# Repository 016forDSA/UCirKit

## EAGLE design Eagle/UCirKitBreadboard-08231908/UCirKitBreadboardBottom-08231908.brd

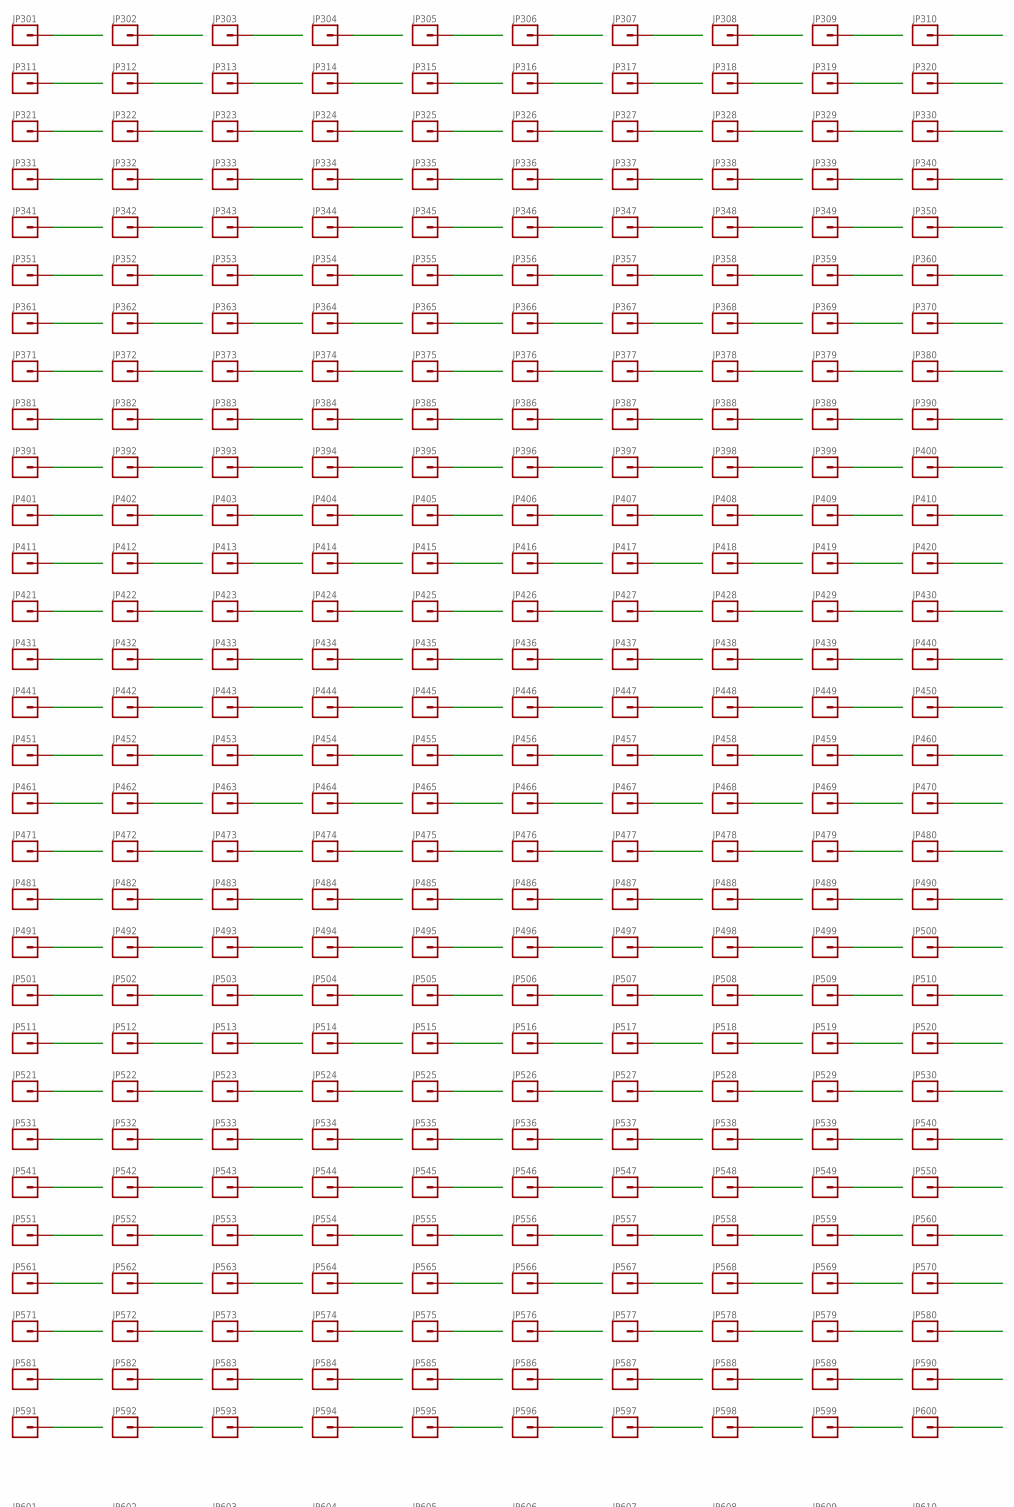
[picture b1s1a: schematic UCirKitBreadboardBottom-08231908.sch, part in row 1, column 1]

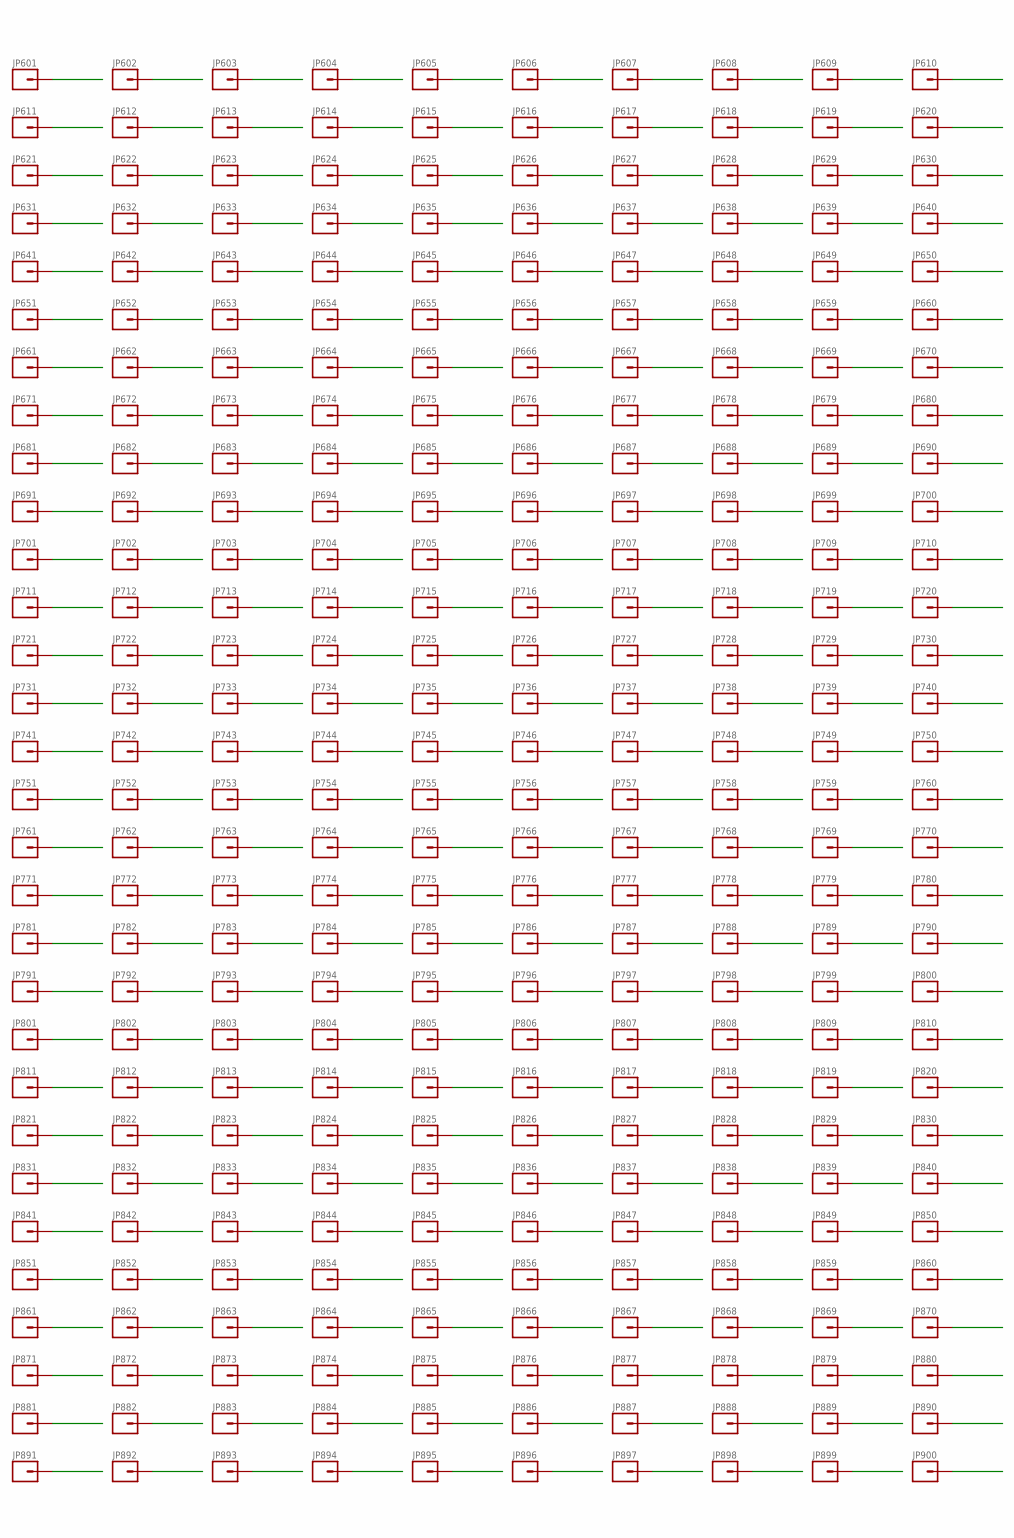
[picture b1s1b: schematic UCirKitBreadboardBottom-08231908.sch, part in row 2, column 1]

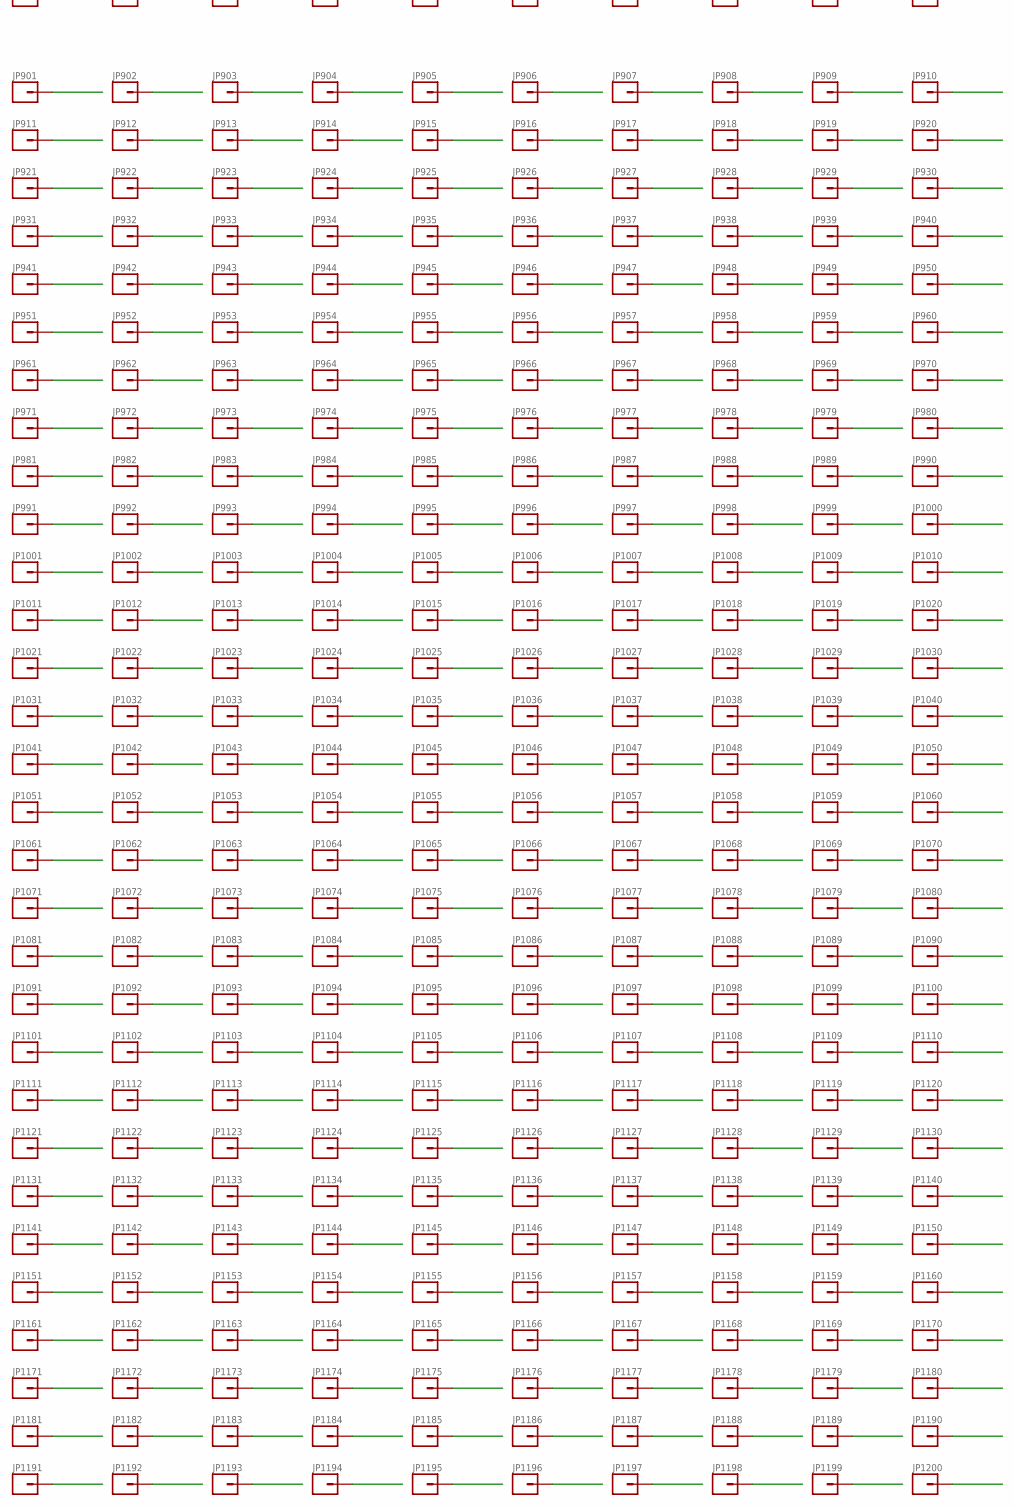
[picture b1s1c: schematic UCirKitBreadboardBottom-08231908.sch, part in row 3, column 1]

Parts:
JP301, JP302, JP303, JP304, JP305, JP306, JP307, JP308, JP309, JP310, JP311, JP312, JP313, JP314, JP315, JP316, JP317, JP318, JP319, JP320, JP321, JP322, JP323, JP324, JP325, JP326, JP327, JP328, JP329, JP330, JP331, JP332, JP333, JP334, JP335, JP336, JP337, JP338, JP339, JP340, JP341, JP342, JP343, JP344, JP345, JP346, JP347, JP348, JP349, JP350, JP351, JP352, JP353, JP354, JP355, JP356, JP357, JP358, JP359, JP360, JP361, JP362, JP363, JP364, JP365, JP366, JP367, JP368, JP369, JP370, JP371, JP372, JP373, JP374, JP375, JP376, JP377, JP378, JP379, JP380, JP381, JP382, JP383, JP384, JP385, JP386, JP387, JP388, JP389, JP390, JP391, JP392, JP393, JP394, JP395, JP396, JP397, JP398, JP399, JP400, JP401, JP402, JP403, JP404, JP405, JP406, JP407, JP408, JP409, JP410, JP411, JP412, JP413, JP414, JP415, JP416, JP417, JP418, JP419, JP420, JP421, JP422, JP423, JP424, JP425, JP426, JP427, JP428, JP429, JP430, JP431, JP432, JP433, JP434, JP435, JP436, JP437, JP438, JP439, JP440, JP441, JP442, JP443, JP444, JP445, JP446, JP447, JP448, JP449, JP450, JP451, JP452, JP453, JP454, JP455, JP456, JP457, JP458, JP459, JP460, JP461, JP462, JP463, JP464, JP465, JP466, JP467, JP468, JP469, JP470, JP471, JP472, JP473, JP474, JP475, JP476, JP477, JP478, JP479, JP480, JP481, JP482, JP483, JP484, JP485, JP486, JP487, JP488, JP489, JP490, JP491, JP492, JP493, JP494, JP495, JP496, JP497, JP498, JP499, JP500, JP501, JP502, JP503, JP504, JP505, JP506, JP507, JP508, JP509, JP510, JP511, JP512, JP513, JP514, JP515, JP516, JP517, JP518, JP519, JP520, JP521, JP522, JP523, JP524, JP525, JP526, JP527, JP528, JP529, JP530, JP531, JP532, JP533, JP534, JP535, JP536, JP537, JP538, JP539, JP540, JP541, JP542, JP543, JP544, JP545, JP546, JP547, JP548, JP549, JP550, JP551, JP552, JP553, JP554, JP555, JP556, JP557, JP558, JP559, JP560, JP561, JP562, JP563, JP564, JP565, JP566, JP567, JP568, JP569, JP570, JP571, JP572, JP573, JP574, JP575, JP576, JP577, JP578, JP579, JP580, JP581, JP582, JP583, JP584, JP585, JP586, JP587, JP588, JP589, JP590, JP591, JP592, JP593, JP594, JP595, JP596, JP597, JP598, JP599, JP600, JP601, JP602, JP603, JP604, JP605, JP606, JP607, JP608, JP609, JP610, JP611, JP612, JP613, JP614, JP615, JP616, JP617, JP618, JP619, JP620, JP621, JP622, JP623, JP624, JP625, JP626, JP627, JP628, JP629, JP630, JP631, JP632, JP633, JP634, JP635, JP636, JP637, JP638, JP639, JP640, JP641, JP642, JP643, JP644, JP645, JP646, JP647, JP648, JP649, JP650, JP651, JP652, JP653, JP654, JP655, JP656, JP657, JP658, JP659, JP660, JP661, JP662, JP663, JP664, JP665, JP666, JP667, JP668, JP669, JP670, JP671, JP672, JP673, JP674, JP675, JP676, JP677, JP678, JP679, JP680, JP681, JP682, JP683, JP684, JP685, JP686, JP687, JP688, JP689, JP690, JP691, JP692, JP693, JP694, JP695, JP696, JP697, JP698, JP699, JP700, JP701, JP702, JP703, JP704, JP705, JP706, JP707, JP708, JP709, JP710, JP711, JP712, JP713, JP714, JP715, JP716, JP717, JP718, JP719, JP720, JP721, JP722, JP723, JP724, JP725, JP726, JP727, JP728, JP729, JP730, JP731, JP732, JP733, JP734, JP735, JP736, JP737, JP738, JP739, JP740, JP741, JP742, JP743, JP744, JP745, JP746, JP747, JP748, JP749, JP750, JP751, JP752, JP753, JP754, JP755, JP756, JP757, JP758, JP759, JP760, JP761, JP762, JP763, JP764, JP765, JP766, JP767, JP768, JP769, JP770, JP771, JP772, JP773, JP774, JP775, JP776, JP777, JP778, JP779, JP780, JP781, JP782, JP783, JP784, JP785, JP786, JP787, JP788, JP789, JP790, JP791, JP792, JP793, JP794, JP795, JP796, JP797, JP798, JP799, JP800, JP801, JP802, JP803, JP804, JP805, JP806, JP807, JP808, JP809, JP810, JP811, JP812, JP813, JP814, JP815, JP816, JP817, JP818, JP819, JP820, JP821, JP822, JP823, JP824, JP825, JP826, JP827, JP828, JP829, JP830, JP831, JP832, JP833, JP834, JP835, JP836, JP837, JP838, JP839, JP840, JP841, JP842, JP843, JP844, JP845, JP846, JP847, JP848, JP849, JP850, JP851, JP852, JP853, JP854, JP855, JP856, JP857, JP858, JP859, JP860, JP861, JP862, JP863, JP864, JP865, JP866, JP867, JP868, JP869, JP870, JP871, JP872, JP873, JP874, JP875, JP876, JP877, JP878, JP879, JP880, JP881, JP882, JP883, JP884, JP885, JP886, JP887, JP888, JP889, JP890, JP891, JP892, JP893, JP894, JP895, JP896, JP897, JP898, JP899, JP900, JP901, JP902, JP903, JP904, JP905, JP906, JP907, JP908, JP909, JP910, JP911, JP912, JP913, JP914, JP915, JP916, JP917, JP918, JP919, JP920, JP921, JP922, JP923, JP924, JP925, JP926, JP927, JP928, JP929, JP930, JP931, JP932, JP933, JP934, JP935, JP936, JP937, JP938, JP939, JP940, JP941, JP942, JP943, JP944, JP945, JP946, JP947, JP948, JP949, JP950, JP951, JP952, JP953, JP954, JP955, JP956, JP957, JP958, JP959, JP960, JP961, JP962, JP963, JP964, JP965, JP966, JP967, JP968, JP969, JP970, JP971, JP972, JP973, JP974, JP975, JP976, JP977, JP978, JP979, JP980, JP981, JP982, JP983, JP984, JP985, JP986, JP987, JP988, JP989, JP990, JP991, JP992, JP993, JP994, JP995, JP996, JP997, JP998, JP999, JP1000, JP1001, JP1002, JP1003, JP1004, JP1005, JP1006, JP1007, JP1008, JP1009, JP1010, JP1011, JP1012, JP1013, JP1014, JP1015, JP1016, JP1017, JP1018, JP1019, JP1020, JP1021, JP1022, JP1023, JP1024, JP1025, JP1026, JP1027, JP1028, JP1029, JP1030, JP1031, JP1032, JP1033, JP1034, JP1035, JP1036, JP1037, JP1038, JP1039, JP1040, JP1041, JP1042, JP1043, JP1044, JP1045, JP1046, JP1047, JP1048, JP1049, JP1050, JP1051, JP1052, JP1053, JP1054, JP1055, JP1056, JP1057, JP1058, JP1059, JP1060, JP1061, JP1062, JP1063, JP1064, JP1065, JP1066, JP1067, JP1068, JP1069, JP1070, JP1071, JP1072, JP1073, JP1074, JP1075, JP1076, JP1077, JP1078, JP1079, JP1080, JP1081, JP1082, JP1083, JP1084, JP1085, JP1086, JP1087, JP1088, JP1089, JP1090, JP1091, JP1092, JP1093, JP1094, JP1095, JP1096, JP1097, JP1098, JP1099, JP1100, JP1101, JP1102, JP1103, JP1104, JP1105, JP1106, JP1107, JP1108, JP1109, JP1110, JP1111, JP1112, JP1113, JP1114, JP1115, JP1116, JP1117, JP1118, JP1119, JP1120, JP1121, JP1122, JP1123, JP1124, JP1125, JP1126, JP1127, JP1128, JP1129, JP1130, JP1131, JP1132, JP1133, JP1134, JP1135, JP1136, JP1137, JP1138, JP1139, JP1140, JP1141, JP1142, JP1143, JP1144, JP1145, JP1146, JP1147, JP1148, JP1149, JP1150, JP1151, JP1152, JP1153, JP1154, JP1155, JP1156, JP1157, JP1158, JP1159, JP1160, JP1161, JP1162, JP1163, JP1164, JP1165, JP1166, JP1167, JP1168, JP1169, JP1170, JP1171, JP1172, JP1173, JP1174, JP1175, JP1176, JP1177, JP1178, JP1179, JP1180, JP1181, JP1182, JP1183, JP1184, JP1185, JP1186, JP1187, JP1188, JP1189, JP1190, JP1191, JP1192, JP1193, JP1194, JP1195, JP1196, JP1197, JP1198, JP1199, JP1200: M01PTH_SMD_3.25X0.85MM_NO_SILK; 1X01_SMD_3.25X0.85MM_NO_SILK

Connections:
0_1440338354: JP301.P$1, JP661.P$1, JP961.P$1
0_1440338422: JP305.P$1, JP851.P$1, JP1151.P$1
0_1440338442: JP306.P$1, JP859.P$1, JP1159.P$1
1_1440338354: JP311.P$1, JP663.P$1, JP963.P$1
1_1440338422: JP315.P$1, JP852.P$1, JP1152.P$1
1_1440338442: JP316.P$1, JP860.P$1, JP1160.P$1
2_1440338354: JP321.P$1, JP665.P$1, JP965.P$1
2_1440338422: JP595.P$1, JP881.P$1, JP1181.P$1
2_1440338442: JP596.P$1, JP889.P$1, JP1189.P$1
3_1440338354: JP331.P$1, JP667.P$1, JP967.P$1
3_1440338422: JP585.P$1, JP882.P$1, JP1182.P$1
3_1440338442: JP586.P$1, JP890.P$1, JP1190.P$1
4_1440338354: JP341.P$1, JP669.P$1, JP969.P$1
4_1440338422: JP325.P$1, JP850.P$1, JP1150.P$1
4_1440338442: JP326.P$1, JP858.P$1, JP1158.P$1
5_1440338354: JP351.P$1, JP671.P$1, JP971.P$1
5_1440338422: JP335.P$1, JP853.P$1, JP1153.P$1
5_1440338442: JP336.P$1, JP861.P$1, JP1161.P$1
6_1440338354: JP361.P$1, JP673.P$1, JP973.P$1
6_1440338422: JP575.P$1, JP880.P$1, JP1180.P$1
6_1440338442: JP576.P$1, JP888.P$1, JP1188.P$1
7_1440338354: JP371.P$1, JP675.P$1, JP975.P$1
7_1440338422: JP565.P$1, JP883.P$1, JP1183.P$1
7_1440338442: JP566.P$1, JP891.P$1, JP1191.P$1
8_1440338354: JP381.P$1, JP677.P$1, JP977.P$1
8_1440338422: JP345.P$1, JP849.P$1, JP1149.P$1
8_1440338442: JP346.P$1, JP857.P$1, JP1157.P$1
9_1440338354: JP391.P$1, JP679.P$1, JP979.P$1
9_1440338422: JP355.P$1, JP854.P$1, JP1154.P$1
9_1440338442: JP356.P$1, JP862.P$1, JP1162.P$1
10_1440338354: JP401.P$1, JP681.P$1, JP981.P$1
10_1440338422: JP555.P$1, JP879.P$1, JP1179.P$1
10_1440338442: JP556.P$1, JP887.P$1, JP1187.P$1
11_1440338354: JP411.P$1, JP683.P$1, JP983.P$1
11_1440338422: JP545.P$1, JP884.P$1, JP1184.P$1
11_1440338442: JP546.P$1, JP892.P$1, JP1192.P$1
12_1440338354: JP421.P$1, JP685.P$1, JP985.P$1
12_1440338422: JP365.P$1, JP848.P$1, JP1148.P$1
12_1440338442: JP366.P$1, JP856.P$1, JP1156.P$1
13_1440338354: JP431.P$1, JP687.P$1, JP987.P$1
13_1440338422: JP375.P$1, JP855.P$1, JP1155.P$1
13_1440338442: JP376.P$1, JP863.P$1, JP1163.P$1
14_1440338354: JP441.P$1, JP689.P$1, JP989.P$1
14_1440338422: JP535.P$1, JP878.P$1, JP1178.P$1
14_1440338442: JP386.P$1, JP864.P$1, JP1164.P$1
15_1440338354: JP451.P$1, JP691.P$1, JP991.P$1
15_1440338422: JP525.P$1, JP885.P$1, JP1185.P$1
15_1440338442: JP396.P$1, JP865.P$1, JP1165.P$1
16_1440338354: JP461.P$1, JP693.P$1, JP993.P$1
16_1440338422: JP385.P$1, JP847.P$1, JP1147.P$1
16_1440338442: JP406.P$1, JP866.P$1, JP1166.P$1
17_1440338354: JP471.P$1, JP695.P$1, JP995.P$1
17_1440338422: JP515.P$1, JP877.P$1, JP1177.P$1
17_1440338442: JP416.P$1, JP867.P$1, JP1167.P$1
18_1440338354: JP481.P$1, JP697.P$1, JP997.P$1
18_1440338422: JP395.P$1, JP846.P$1, JP1146.P$1
18_1440338442: JP426.P$1, JP868.P$1, JP1168.P$1
19_1440338354: JP491.P$1, JP699.P$1, JP999.P$1
19_1440338422: JP505.P$1, JP876.P$1, JP1176.P$1
19_1440338442: JP436.P$1, JP869.P$1, JP1169.P$1
20_1440338354: JP501.P$1, JP701.P$1, JP1001.P$1
20_1440338422: JP405.P$1, JP845.P$1, JP1145.P$1
20_1440338442: JP446.P$1, JP870.P$1, JP1170.P$1
21_1440338354: JP511.P$1, JP703.P$1, JP1003.P$1
21_1440338422: JP495.P$1, JP875.P$1, JP1175.P$1
21_1440338442: JP536.P$1, JP886.P$1, JP1186.P$1
22_1440338354: JP521.P$1, JP705.P$1, JP1005.P$1
22_1440338422: JP415.P$1, JP844.P$1, JP1144.P$1
22_1440338442: JP526.P$1, JP893.P$1, JP1193.P$1
23_1440338354: JP531.P$1, JP707.P$1, JP1007.P$1
23_1440338422: JP485.P$1, JP874.P$1, JP1174.P$1
23_1440338442: JP516.P$1, JP894.P$1, JP1194.P$1
24_1440338354: JP541.P$1, JP709.P$1, JP1009.P$1
24_1440338422: JP425.P$1, JP843.P$1, JP1143.P$1
24_1440338442: JP506.P$1, JP895.P$1, JP1195.P$1
25_1440338354: JP551.P$1, JP711.P$1, JP1011.P$1
25_1440338422: JP475.P$1, JP873.P$1, JP1173.P$1
25_1440338442: JP496.P$1, JP896.P$1, JP1196.P$1
26_1440338354: JP561.P$1, JP713.P$1, JP1013.P$1
26_1440338422: JP435.P$1, JP842.P$1, JP1142.P$1
26_1440338442: JP486.P$1, JP897.P$1, JP1197.P$1
27_1440338354: JP571.P$1, JP715.P$1, JP1015.P$1
27_1440338422: JP465.P$1, JP872.P$1, JP1172.P$1
27_1440338442: JP476.P$1, JP898.P$1, JP1198.P$1
28_1440338354: JP581.P$1, JP717.P$1, JP1017.P$1
28_1440338422: JP445.P$1, JP841.P$1, JP1141.P$1
28_1440338442: JP466.P$1, JP899.P$1, JP1199.P$1
29_1440338354: JP591.P$1, JP719.P$1, JP1019.P$1
29_1440338422: JP455.P$1, JP871.P$1, JP1171.P$1
29_1440338442: JP456.P$1, JP900.P$1, JP1200.P$1
30_1440338354: JP592.P$1, JP720.P$1, JP1020.P$1
31_1440338354: JP310.P$1, JP721.P$1, JP1021.P$1
32_1440338354: JP320.P$1, JP723.P$1, JP1023.P$1
33_1440338354: JP330.P$1, JP725.P$1, JP1025.P$1
34_1440338354: JP340.P$1, JP727.P$1, JP1027.P$1
35_1440338354: JP350.P$1, JP729.P$1, JP1029.P$1
36_1440338354: JP360.P$1, JP731.P$1, JP1031.P$1
37_1440338354: JP370.P$1, JP733.P$1, JP1033.P$1
38_1440338354: JP380.P$1, JP735.P$1, JP1035.P$1
39_1440338354: JP390.P$1, JP737.P$1, JP1037.P$1
40_1440338354: JP400.P$1, JP739.P$1, JP1039.P$1
41_1440338354: JP410.P$1, JP741.P$1, JP1041.P$1
42_1440338354: JP420.P$1, JP743.P$1, JP1043.P$1
43_1440338354: JP430.P$1, JP745.P$1, JP1045.P$1
44_1440338354: JP440.P$1, JP747.P$1, JP1047.P$1
45_1440338354: JP450.P$1, JP749.P$1, JP1049.P$1
46_1440338354: JP460.P$1, JP751.P$1, JP1051.P$1
47_1440338354: JP470.P$1, JP753.P$1, JP1053.P$1
48_1440338354: JP480.P$1, JP755.P$1, JP1055.P$1
49_1440338354: JP490.P$1, JP757.P$1, JP1057.P$1
50_1440338354: JP500.P$1, JP759.P$1, JP1059.P$1
51_1440338354: JP510.P$1, JP761.P$1, JP1061.P$1
52_1440338354: JP520.P$1, JP763.P$1, JP1063.P$1
53_1440338354: JP530.P$1, JP765.P$1, JP1065.P$1
54_1440338354: JP540.P$1, JP767.P$1, JP1067.P$1
55_1440338354: JP550.P$1, JP769.P$1, JP1069.P$1
56_1440338354: JP560.P$1, JP771.P$1, JP1071.P$1
57_1440338354: JP570.P$1, JP773.P$1, JP1073.P$1
58_1440338354: JP580.P$1, JP775.P$1, JP1075.P$1
59_1440338354: JP590.P$1, JP777.P$1, JP1077.P$1
60_1440338354: JP600.P$1, JP779.P$1, JP1079.P$1
61_1440338354: JP599.P$1, JP780.P$1, JP1080.P$1
62_1440338354: JP302.P$1, JP662.P$1, JP962.P$1
63_1440338354: JP312.P$1, JP664.P$1, JP964.P$1
64_1440338354: JP322.P$1, JP666.P$1, JP966.P$1
65_1440338354: JP332.P$1, JP668.P$1, JP968.P$1
66_1440338354: JP342.P$1, JP670.P$1, JP970.P$1
67_1440338354: JP352.P$1, JP672.P$1, JP972.P$1
68_1440338354: JP362.P$1, JP674.P$1, JP974.P$1
69_1440338354: JP372.P$1, JP676.P$1, JP976.P$1
70_1440338354: JP382.P$1, JP678.P$1, JP978.P$1
71_1440338354: JP392.P$1, JP680.P$1, JP980.P$1
72_1440338354: JP402.P$1, JP682.P$1, JP982.P$1
73_1440338354: JP412.P$1, JP684.P$1, JP984.P$1
74_1440338354: JP422.P$1, JP686.P$1, JP986.P$1
75_1440338354: JP432.P$1, JP688.P$1, JP988.P$1
76_1440338354: JP442.P$1, JP690.P$1, JP990.P$1
77_1440338354: JP452.P$1, JP692.P$1, JP992.P$1
78_1440338354: JP462.P$1, JP694.P$1, JP994.P$1
79_1440338354: JP472.P$1, JP696.P$1, JP996.P$1
80_1440338354: JP482.P$1, JP698.P$1, JP998.P$1
81_1440338354: JP492.P$1, JP700.P$1, JP1000.P$1
82_1440338354: JP502.P$1, JP702.P$1, JP1002.P$1
83_1440338354: JP512.P$1, JP704.P$1, JP1004.P$1
84_1440338354: JP522.P$1, JP706.P$1, JP1006.P$1
85_1440338354: JP532.P$1, JP708.P$1, JP1008.P$1
86_1440338354: JP542.P$1, JP710.P$1, JP1010.P$1
87_1440338354: JP552.P$1, JP712.P$1, JP1012.P$1
88_1440338354: JP562.P$1, JP714.P$1, JP1014.P$1
89_1440338354: JP572.P$1, JP716.P$1, JP1016.P$1
90_1440338354: JP582.P$1, JP718.P$1, JP1018.P$1
91_1440338354: JP309.P$1, JP722.P$1, JP1022.P$1
92_1440338354: JP319.P$1, JP724.P$1, JP1024.P$1
93_1440338354: JP329.P$1, JP726.P$1, JP1026.P$1
94_1440338354: JP339.P$1, JP728.P$1, JP1028.P$1
95_1440338354: JP349.P$1, JP730.P$1, JP1030.P$1
96_1440338354: JP359.P$1, JP732.P$1, JP1032.P$1
97_1440338354: JP369.P$1, JP734.P$1, JP1034.P$1
98_1440338354: JP379.P$1, JP736.P$1, JP1036.P$1
99_1440338354: JP389.P$1, JP738.P$1, JP1038.P$1
100_1440338354: JP399.P$1, JP740.P$1, JP1040.P$1
101_1440338354: JP409.P$1, JP742.P$1, JP1042.P$1
102_1440338354: JP419.P$1, JP744.P$1, JP1044.P$1
103_1440338354: JP429.P$1, JP746.P$1, JP1046.P$1
104_1440338354: JP439.P$1, JP748.P$1, JP1048.P$1
105_1440338354: JP449.P$1, JP750.P$1, JP1050.P$1
106_1440338354: JP459.P$1, JP752.P$1, JP1052.P$1
107_1440338354: JP469.P$1, JP754.P$1, JP1054.P$1
108_1440338354: JP479.P$1, JP756.P$1, JP1056.P$1
109_1440338354: JP489.P$1, JP758.P$1, JP1058.P$1
110_1440338354: JP499.P$1, JP760.P$1, JP1060.P$1
111_1440338354: JP509.P$1, JP762.P$1, JP1062.P$1
112_1440338354: JP519.P$1, JP764.P$1, JP1064.P$1
113_1440338354: JP529.P$1, JP766.P$1, JP1066.P$1
114_1440338354: JP539.P$1, JP768.P$1, JP1068.P$1
115_1440338354: JP549.P$1, JP770.P$1, JP1070.P$1
116_1440338354: JP559.P$1, JP772.P$1, JP1072.P$1
117_1440338354: JP569.P$1, JP774.P$1, JP1074.P$1
118_1440338354: JP579.P$1, JP776.P$1, JP1076.P$1
119_1440338354: JP589.P$1, JP778.P$1, JP1078.P$1
120_1440338354: JP308.P$1, JP781.P$1, JP1081.P$1
121_1440338354: JP318.P$1, JP783.P$1, JP1083.P$1
122_1440338354: JP328.P$1, JP785.P$1, JP1085.P$1
123_1440338354: JP338.P$1, JP787.P$1, JP1087.P$1
124_1440338354: JP348.P$1, JP789.P$1, JP1089.P$1
125_1440338354: JP358.P$1, JP791.P$1, JP1091.P$1
126_1440338354: JP368.P$1, JP793.P$1, JP1093.P$1
127_1440338354: JP378.P$1, JP795.P$1, JP1095.P$1
128_1440338354: JP388.P$1, JP797.P$1, JP1097.P$1
129_1440338354: JP398.P$1, JP799.P$1, JP1099.P$1
130_1440338354: JP408.P$1, JP801.P$1, JP1101.P$1
131_1440338354: JP418.P$1, JP803.P$1, JP1103.P$1
132_1440338354: JP428.P$1, JP805.P$1, JP1105.P$1
133_1440338354: JP438.P$1, JP807.P$1, JP1107.P$1
134_1440338354: JP448.P$1, JP809.P$1, JP1109.P$1
135_1440338354: JP458.P$1, JP811.P$1, JP1111.P$1
136_1440338354: JP468.P$1, JP813.P$1, JP1113.P$1
137_1440338354: JP478.P$1, JP815.P$1, JP1115.P$1
138_1440338354: JP488.P$1, JP817.P$1, JP1117.P$1
139_1440338354: JP498.P$1, JP819.P$1, JP1119.P$1
140_1440338354: JP508.P$1, JP821.P$1, JP1121.P$1
141_1440338354: JP518.P$1, JP823.P$1, JP1123.P$1
142_1440338354: JP528.P$1, JP825.P$1, JP1125.P$1
143_1440338354: JP538.P$1, JP827.P$1, JP1127.P$1
144_1440338354: JP548.P$1, JP829.P$1, JP1129.P$1
145_1440338354: JP558.P$1, JP831.P$1, JP1131.P$1
146_1440338354: JP568.P$1, JP833.P$1, JP1133.P$1
147_1440338354: JP578.P$1, JP835.P$1, JP1135.P$1
148_1440338354: JP588.P$1, JP837.P$1, JP1137.P$1
149_1440338354: JP598.P$1, JP839.P$1, JP1139.P$1
150_1440338354: JP597.P$1, JP840.P$1, JP1140.P$1
151_1440338354: JP303.P$1, JP601.P$1, JP901.P$1
152_1440338354: JP313.P$1, JP603.P$1, JP903.P$1
153_1440338354: JP323.P$1, JP605.P$1, JP905.P$1
154_1440338354: JP333.P$1, JP607.P$1, JP907.P$1
155_1440338354: JP343.P$1, JP609.P$1, JP909.P$1
156_1440338354: JP353.P$1, JP611.P$1, JP911.P$1
157_1440338354: JP363.P$1, JP613.P$1, JP913.P$1
158_1440338354: JP373.P$1, JP615.P$1, JP915.P$1
159_1440338354: JP383.P$1, JP617.P$1, JP917.P$1
160_1440338354: JP393.P$1, JP619.P$1, JP919.P$1
161_1440338354: JP403.P$1, JP621.P$1, JP921.P$1
162_1440338354: JP413.P$1, JP623.P$1, JP923.P$1
163_1440338354: JP423.P$1, JP625.P$1, JP925.P$1
164_1440338354: JP433.P$1, JP627.P$1, JP927.P$1
165_1440338354: JP443.P$1, JP629.P$1, JP929.P$1
166_1440338354: JP453.P$1, JP631.P$1, JP931.P$1
167_1440338354: JP463.P$1, JP633.P$1, JP933.P$1
168_1440338354: JP473.P$1, JP635.P$1, JP935.P$1
169_1440338354: JP483.P$1, JP637.P$1, JP937.P$1
170_1440338354: JP493.P$1, JP639.P$1, JP939.P$1
171_1440338354: JP503.P$1, JP641.P$1, JP941.P$1
172_1440338354: JP513.P$1, JP643.P$1, JP943.P$1
173_1440338354: JP523.P$1, JP645.P$1, JP945.P$1
174_1440338354: JP533.P$1, JP647.P$1, JP947.P$1
175_1440338354: JP543.P$1, JP649.P$1, JP949.P$1
176_1440338354: JP553.P$1, JP651.P$1, JP951.P$1
177_1440338354: JP563.P$1, JP653.P$1, JP953.P$1
178_1440338354: JP573.P$1, JP655.P$1, JP955.P$1
179_1440338354: JP583.P$1, JP657.P$1, JP957.P$1
180_1440338354: JP593.P$1, JP659.P$1, JP959.P$1
181_1440338354: JP594.P$1, JP660.P$1, JP960.P$1
182_1440338354: JP307.P$1, JP782.P$1, JP1082.P$1
183_1440338354: JP317.P$1, JP784.P$1, JP1084.P$1
184_1440338354: JP327.P$1, JP786.P$1, JP1086.P$1
185_1440338354: JP337.P$1, JP788.P$1, JP1088.P$1
186_1440338354: JP347.P$1, JP790.P$1, JP1090.P$1
187_1440338354: JP357.P$1, JP792.P$1, JP1092.P$1
188_1440338354: JP367.P$1, JP794.P$1, JP1094.P$1
189_1440338354: JP377.P$1, JP796.P$1, JP1096.P$1
190_1440338354: JP387.P$1, JP798.P$1, JP1098.P$1
191_1440338354: JP397.P$1, JP800.P$1, JP1100.P$1
192_1440338354: JP407.P$1, JP802.P$1, JP1102.P$1
193_1440338354: JP417.P$1, JP804.P$1, JP1104.P$1
194_1440338354: JP427.P$1, JP806.P$1, JP1106.P$1
195_1440338354: JP437.P$1, JP808.P$1, JP1108.P$1
196_1440338354: JP447.P$1, JP810.P$1, JP1110.P$1
197_1440338354: JP457.P$1, JP812.P$1, JP1112.P$1
198_1440338354: JP467.P$1, JP814.P$1, JP1114.P$1
199_1440338354: JP477.P$1, JP816.P$1, JP1116.P$1
200_1440338354: JP487.P$1, JP818.P$1, JP1118.P$1
201_1440338354: JP497.P$1, JP820.P$1, JP1120.P$1
202_1440338354: JP507.P$1, JP822.P$1, JP1122.P$1
203_1440338354: JP517.P$1, JP824.P$1, JP1124.P$1
204_1440338354: JP527.P$1, JP826.P$1, JP1126.P$1
205_1440338354: JP537.P$1, JP828.P$1, JP1128.P$1
206_1440338354: JP547.P$1, JP830.P$1, JP1130.P$1
207_1440338354: JP557.P$1, JP832.P$1, JP1132.P$1
208_1440338354: JP567.P$1, JP834.P$1, JP1134.P$1
209_1440338354: JP577.P$1, JP836.P$1, JP1136.P$1
210_1440338354: JP587.P$1, JP838.P$1, JP1138.P$1
211_1440338354: JP304.P$1, JP602.P$1, JP902.P$1
212_1440338354: JP314.P$1, JP604.P$1, JP904.P$1
213_1440338354: JP324.P$1, JP606.P$1, JP906.P$1
214_1440338354: JP334.P$1, JP608.P$1, JP908.P$1
215_1440338354: JP344.P$1, JP610.P$1, JP910.P$1
216_1440338354: JP354.P$1, JP612.P$1, JP912.P$1
217_1440338354: JP364.P$1, JP614.P$1, JP914.P$1
218_1440338354: JP374.P$1, JP616.P$1, JP916.P$1
219_1440338354: JP384.P$1, JP618.P$1, JP918.P$1
220_1440338354: JP394.P$1, JP620.P$1, JP920.P$1
221_1440338354: JP404.P$1, JP622.P$1, JP922.P$1
222_1440338354: JP414.P$1, JP624.P$1, JP924.P$1
223_1440338354: JP424.P$1, JP626.P$1, JP926.P$1
224_1440338354: JP434.P$1, JP628.P$1, JP928.P$1
225_1440338354: JP444.P$1, JP630.P$1, JP930.P$1
226_1440338354: JP454.P$1, JP632.P$1, JP932.P$1
227_1440338354: JP464.P$1, JP634.P$1, JP934.P$1
228_1440338354: JP474.P$1, JP636.P$1, JP936.P$1
229_1440338354: JP484.P$1, JP638.P$1, JP938.P$1
230_1440338354: JP494.P$1, JP640.P$1, JP940.P$1
231_1440338354: JP504.P$1, JP642.P$1, JP942.P$1
232_1440338354: JP514.P$1, JP644.P$1, JP944.P$1
233_1440338354: JP524.P$1, JP646.P$1, JP946.P$1
234_1440338354: JP534.P$1, JP648.P$1, JP948.P$1
235_1440338354: JP544.P$1, JP650.P$1, JP950.P$1
236_1440338354: JP554.P$1, JP652.P$1, JP952.P$1
237_1440338354: JP564.P$1, JP654.P$1, JP954.P$1
238_1440338354: JP574.P$1, JP656.P$1, JP956.P$1
239_1440338354: JP584.P$1, JP658.P$1, JP958.P$1

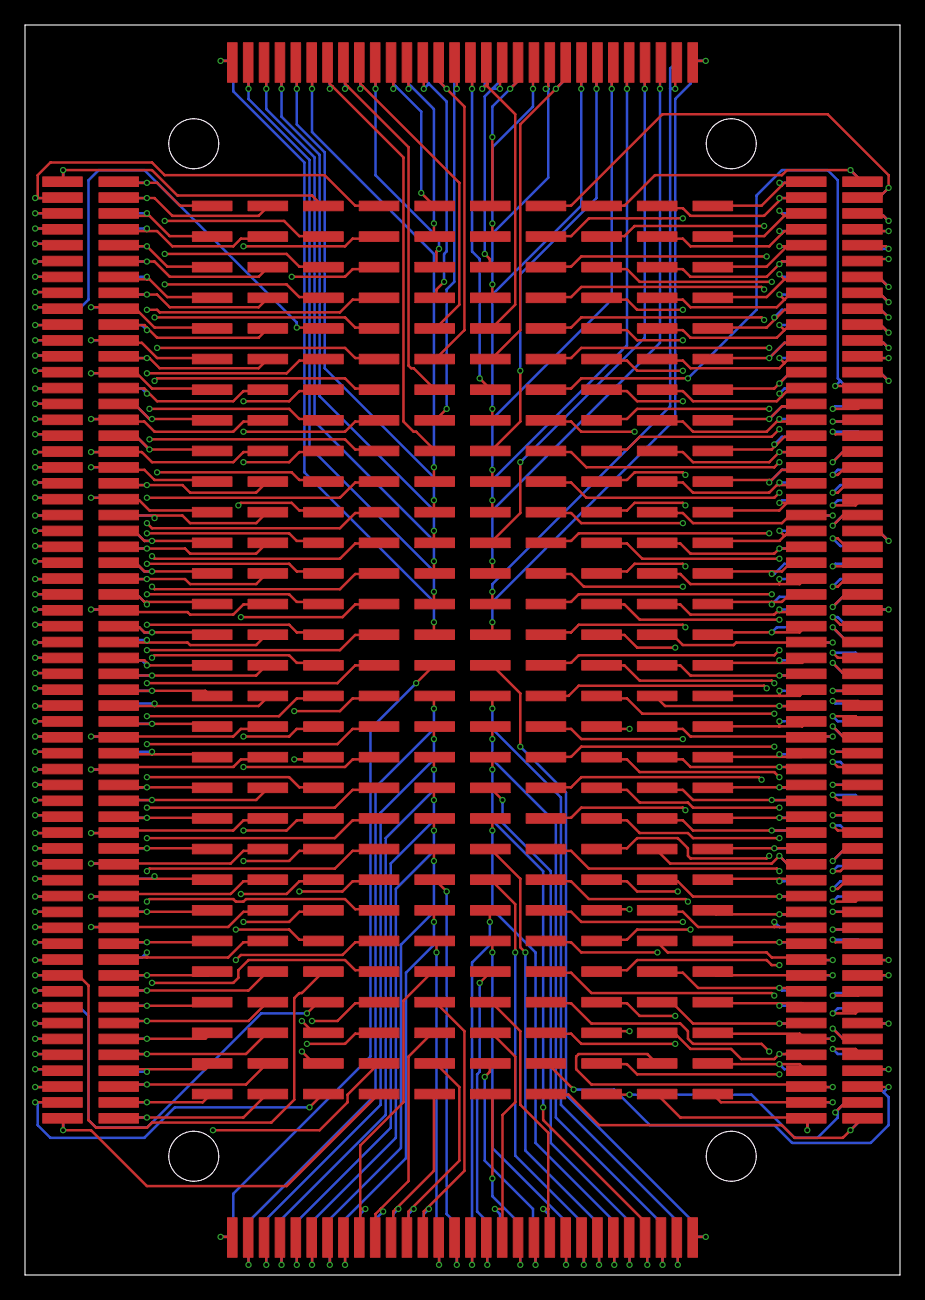
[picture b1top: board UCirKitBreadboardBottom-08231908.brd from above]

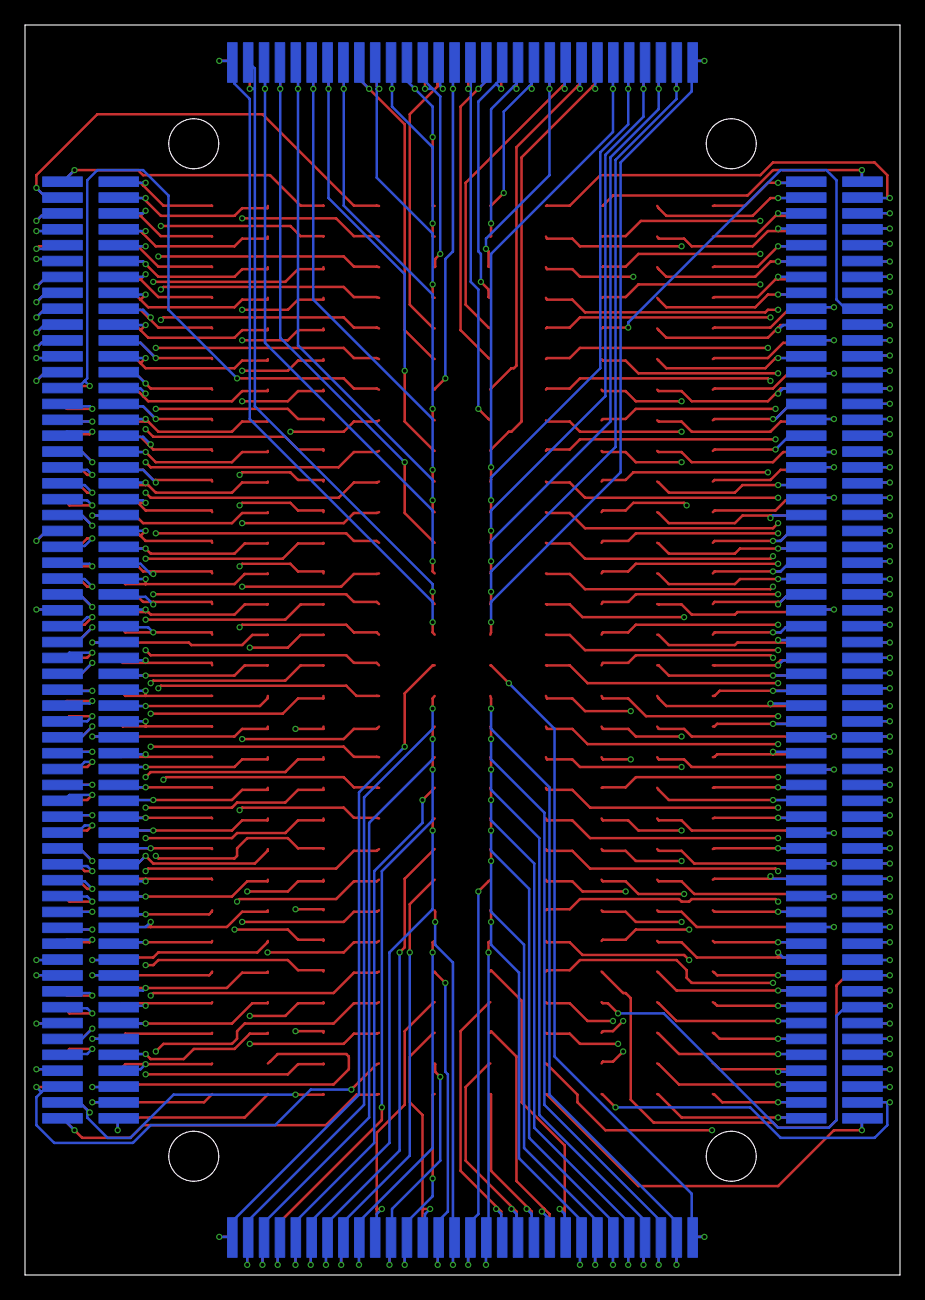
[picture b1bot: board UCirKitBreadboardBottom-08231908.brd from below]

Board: 4 copper layers, 70.0 x 100.0 mm, 900 parts (300 on the bottom side), 300 nets.

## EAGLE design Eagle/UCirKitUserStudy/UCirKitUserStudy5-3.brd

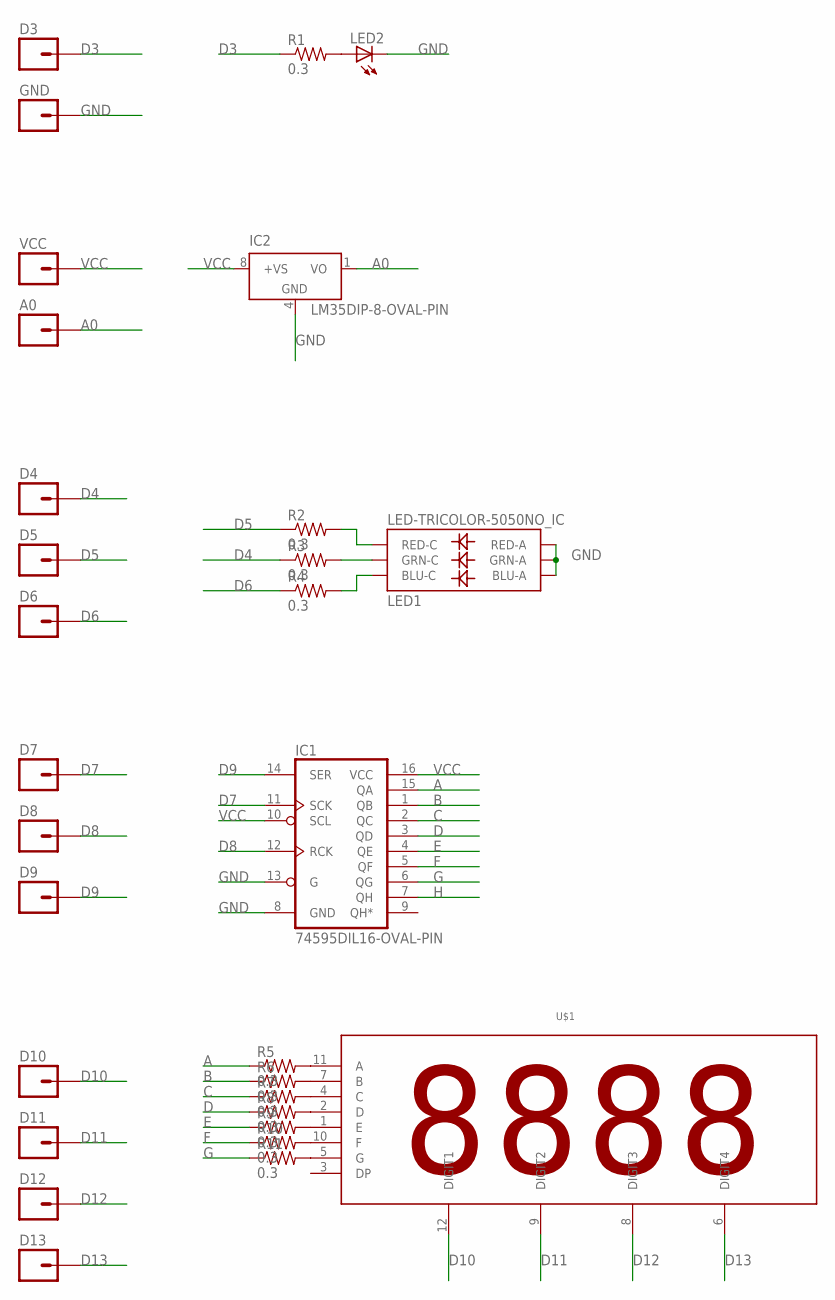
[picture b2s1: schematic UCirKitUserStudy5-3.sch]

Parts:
A0: M01OVAL_PIN; 1X01_OVAL_PIN
D3, D4, D5, D6, D7, D8, D9, D10, D11, D12, D13: M01OVAL_PIN; 1X01_OVAL_PIN
GND: M01OVAL_PIN; 1X01_OVAL_PIN
IC1: 74595DIL16-OVAL-PIN; DIL16-OVAL-PIN
IC2: LM35DIP-8-OVAL-PIN; DIP-8-OVAL-PIN
LED1: LED-TRICOLOR-5050NO_IC; LED-TRICOLOR-5050
LED2: LEDCHIP-LED0805; CHIP-LED0805
R1, R2, R3, R4, R5, R6, R7, R8, R9, R10, R11: 0.3; 0805
U$1: 4DIGIT_SEVEN_SEGMENT4DIGIT_SEVEN_SEGMENT_OVAL_PIN; 4DIGIT_SEVEN_SEGMENT_OVAL_PIN
VCC: M01OVAL_PIN; 1X01_OVAL_PIN

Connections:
A: IC1.15 (QA), R5.1
A0: A0.1, IC2.1 (VO)
B: IC1.1 (QB), R6.1
C: IC1.2 (QC), R7.1
D: IC1.3 (QD), R8.1
D3: D3.1, R1.1
D4: D4.1, R3.1
D5: D5.1, R2.1
D6: D6.1, R4.1
D7: D7.1, IC1.11 (SCK)
D8: D8.1, IC1.12 (RCK)
D9: D9.1, IC1.14 (SER)
D10: D10.1, U$1.12 (DIGIT1)
D11: D11.1, U$1.9 (DIGIT2)
D12: D12.1, U$1.8 (DIGIT3)
D13: D13.1, U$1.6 (DIGIT4)
E: IC1.4 (QE), R9.1
F: IC1.5 (QF), R10.1
G: IC1.6 (QG), R11.1
GND: GND.1, IC1.8 (GND), IC1.13 (G), IC2.4 (GND), LED1.1 (GRN-A), LED1.2 (RED-A), LED1.3 (BLU-A), LED2.C
H: IC1.7 (QH)
unnamed: R5.2, U$1.11 (A)
unnamed: R6.2, U$1.7 (B)
unnamed: R7.2, U$1.4 (C)
unnamed: R8.2, U$1.2 (D)
unnamed: R9.2, U$1.1 (E)
unnamed: R10.2, U$1.10 (F)
unnamed: R11.2, U$1.5 (G)
unnamed: LED1.5 (RED-C), R2.2
unnamed: LED1.6 (GRN-C), R3.2
unnamed: LED1.4 (BLU-C), R4.2
unnamed: LED2.A, R1.2
VCC: IC1.10 (SCL), IC1.16 (VCC), IC2.8 (+VS), VCC.1

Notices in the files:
parts and their libraries:
SparkFun-Connectors: Licensing: Creative Commons ShareAlike 4.0 International - https://creativecommons.org/licenses/by-sa/4.0
